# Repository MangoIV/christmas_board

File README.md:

# christmas_board
you want a cheap macropad with a christmas theming? here you go.

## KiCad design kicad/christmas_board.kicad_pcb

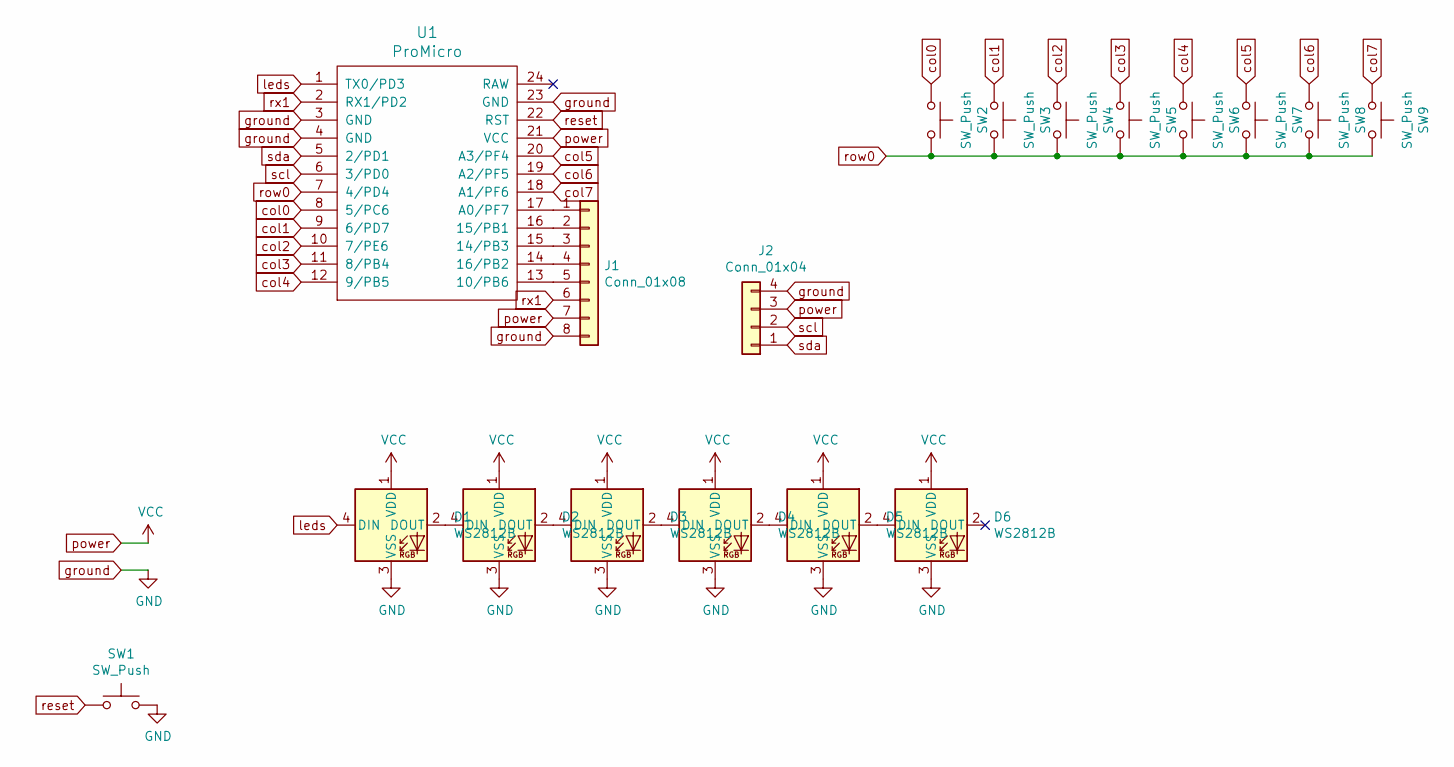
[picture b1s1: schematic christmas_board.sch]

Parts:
D1, D2, D3, D4, D5, D6: WS2812B; LED_WS2812B_PLCC4_5.0x5.0mm_P3.2mm
J1: Conn_01x08; PinHeader_2x04_P2.00mm_Vertical
J2: Conn_01x04; OLED
SW1: SW_Push; SW_SPST_TL3342
SW2, SW3, SW4, SW5, SW6, SW7, SW8, SW9: SW_Push; MX-Alps-Choc-1U-NoLED
U1: ProMicro; ArduinoProMicro-BackSide

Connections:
unnamed: D1.2 (DOUT), D2.4 (DIN)
unnamed: D2.2 (DOUT), D3.4 (DIN)
unnamed: D3.2 (DOUT), D4.4 (DIN)
unnamed: D4.2 (DOUT), D5.4 (DIN)
unnamed: D5.2 (DOUT), D6.4 (DIN)
unnamed 5: D6.2 (DOUT); also elsewhere on the board
unnamed: J1.1, U1.17 (A0/PF7)
unnamed: J1.2, U1.16 (15/PB1)
unnamed: J1.3, U1.15 (14/PB3)
unnamed: J1.4, U1.14 (16/PB2)
unnamed: J1.5, U1.13 (10/PB6)
col0: SW2.1, U1.8 (5/PC6)
col1: SW3.1, U1.9 (6/PD7)
col2: SW4.1, U1.10 (7/PE6)
col3: SW5.1, U1.11 (8/PB4)
col4: SW6.1, U1.12 (9/PB5)
col5: SW7.1, U1.20 (A3/PF4)
col6: SW8.1, U1.19 (A2/PF5)
col7: SW9.1, U1.18 (A1/PF6)
ground: D1.3 (VSS), D2.3 (VSS), D3.3 (VSS), D4.3 (VSS), D5.3 (VSS), D6.3 (VSS), J1.8, J2.4, SW1.2, U1.3 (GND), U1.4 (GND), U1.23 (GND); also elsewhere on the board
leds: D1.4 (DIN), U1.1 (TX0/PD3)
power: D1.1 (VDD), D2.1 (VDD), D3.1 (VDD), D4.1 (VDD), D5.1 (VDD), D6.1 (VDD), J1.7, J2.3, U1.21 (VCC); also elsewhere on the board
reset: SW1.1, U1.22 (RST)
row0: SW2.2, SW3.2, SW4.2, SW5.2, SW6.2, SW7.2, SW8.2, SW9.2, U1.7 (4/PD4)
rx1: J1.6, U1.2 (RX1/PD2)
scl: J2.2, U1.6 (3/PD0)
sda: J2.1, U1.5 (2/PD1)

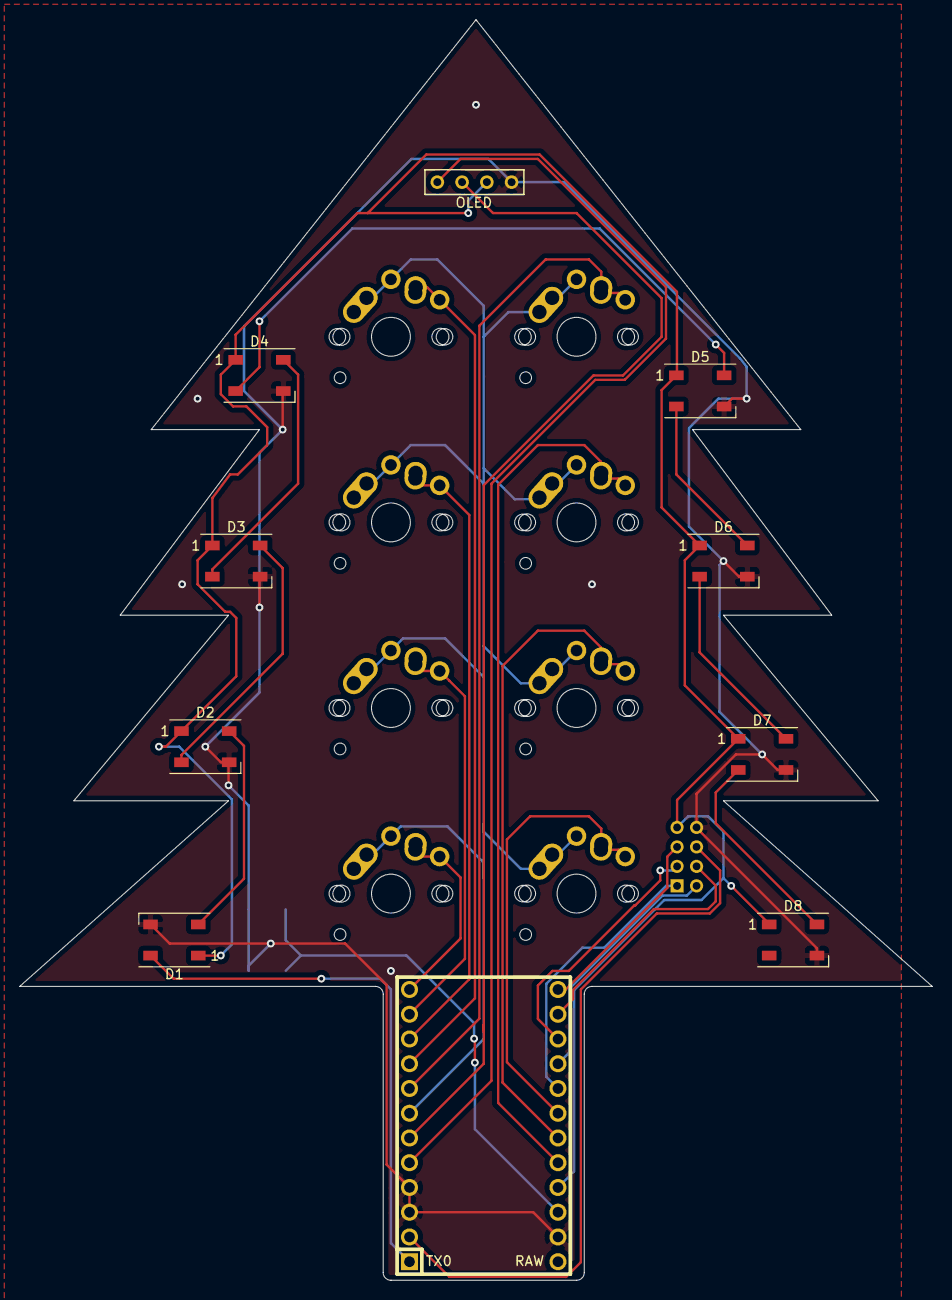
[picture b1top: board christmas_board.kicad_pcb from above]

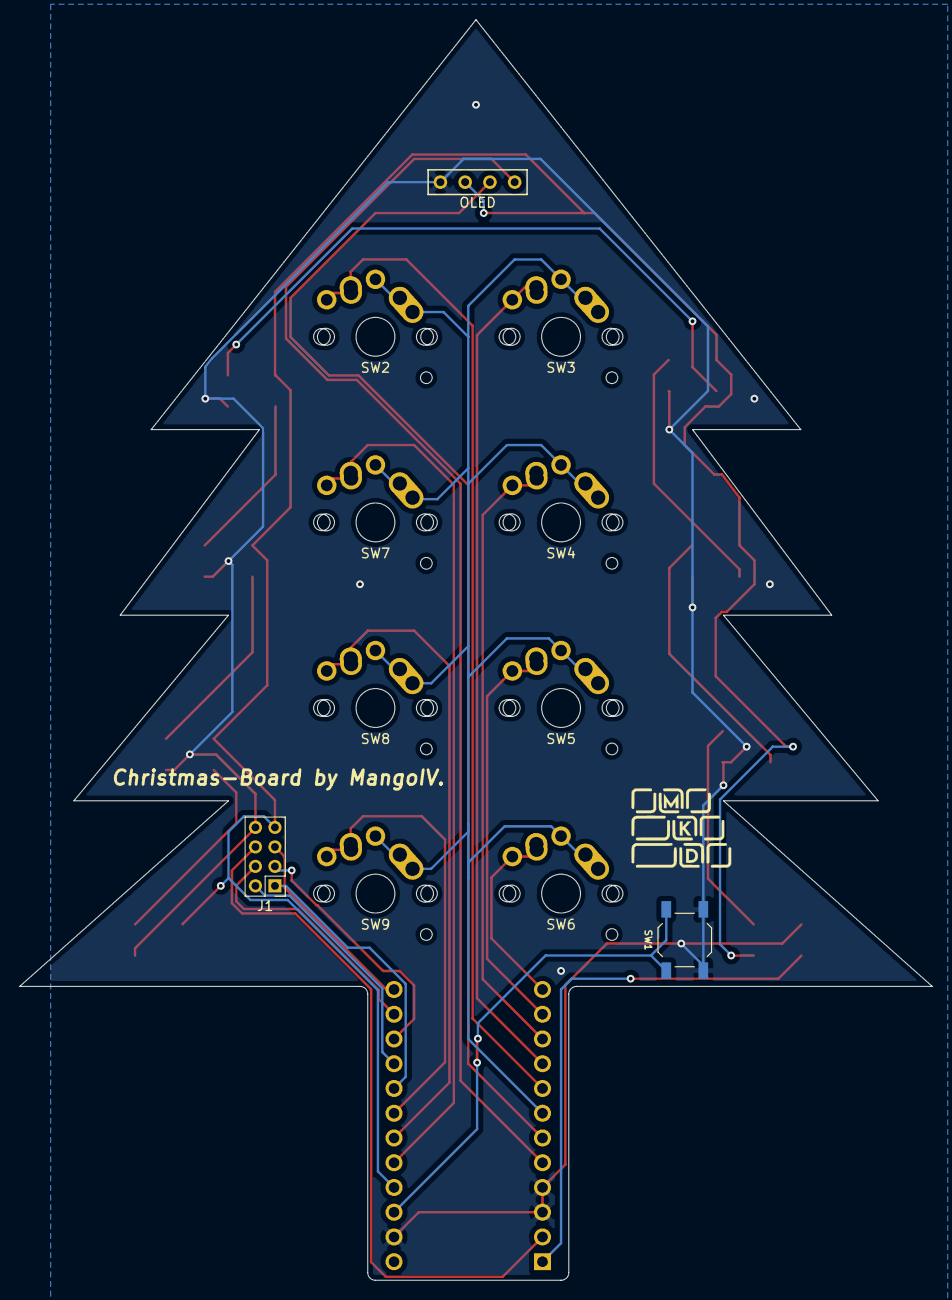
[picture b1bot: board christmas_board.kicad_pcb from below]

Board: 2 copper layers, 93.7 x 129.4 mm, 20 parts (4 on the bottom side), 28 nets.

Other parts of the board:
D7, D8: WS2812B; LED_WS2812B_PLCC4_5.0x5.0mm_P3.2mm

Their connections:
unnamed 5: D7.4; also elsewhere on the board
unnamed: D7.2, D8.4
ground: D7.3, D8.3; also elsewhere on the board
power: D7.1, D8.1; also elsewhere on the board

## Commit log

2020-12-03 added submodules
2020-12-03 finished schematics
2020-12-03 finished routing, added graphics
2020-12-03 added silkscreen, ran drc, output production files
2021-12-07 mkd logo rauf geklatscht klappt aber noch net
2021-12-07 fixed
